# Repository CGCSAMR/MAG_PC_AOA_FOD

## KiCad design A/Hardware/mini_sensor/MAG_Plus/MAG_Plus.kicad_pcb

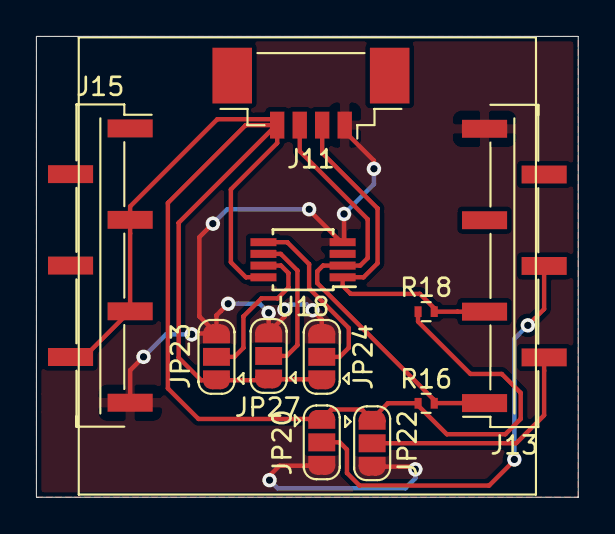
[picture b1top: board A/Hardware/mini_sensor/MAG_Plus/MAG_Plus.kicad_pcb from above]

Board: 2 copper layers, 30.1 x 25.6 mm, 11 parts (0 on the bottom side), 9 nets.

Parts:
J11: Conn_01x04_Male; Molex_PicoBlade_53398-0471_04x1.25mm_Straight
J13, J15: Conn_01x07_Female; Pin_Header_Straight_1x07_Pitch2.54mm_SMD_Pin1Right
JP20, JP22, JP23, JP24, JP27: Jumper_3_Open; SolderJumper-3_P1.3mm_Open_RoundedPad1.0x1.5mm
R16, R18: R; R_0402
U18: MCP9804_MSOP; MSOP-8_3x3mm_Pitch0.65mm

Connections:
GND: J11.1, J13.7, J15.7, JP20.3, JP22.3, JP23.3, JP24.3, JP27.3, U18.4
MAG2_A0: JP23.2, U18.7
MAG2_A1: JP27.2, U18.6
MAG2_A2: JP24.2, U18.5
MAG2_BIT0: J13.4, JP20.2
MAG2_BIT1: J13.2, JP22.2
MAG_3V3: J11.4, J15.3, J15.5, J15.6, JP20.1, JP22.1, JP23.1, JP24.1, JP27.1, R16.1, R18.1, U18.8
RPI_SCL: J11.3, J13.1, R16.2, U18.2
RPI_SDA: J11.2, J13.3, R18.2, U18.1

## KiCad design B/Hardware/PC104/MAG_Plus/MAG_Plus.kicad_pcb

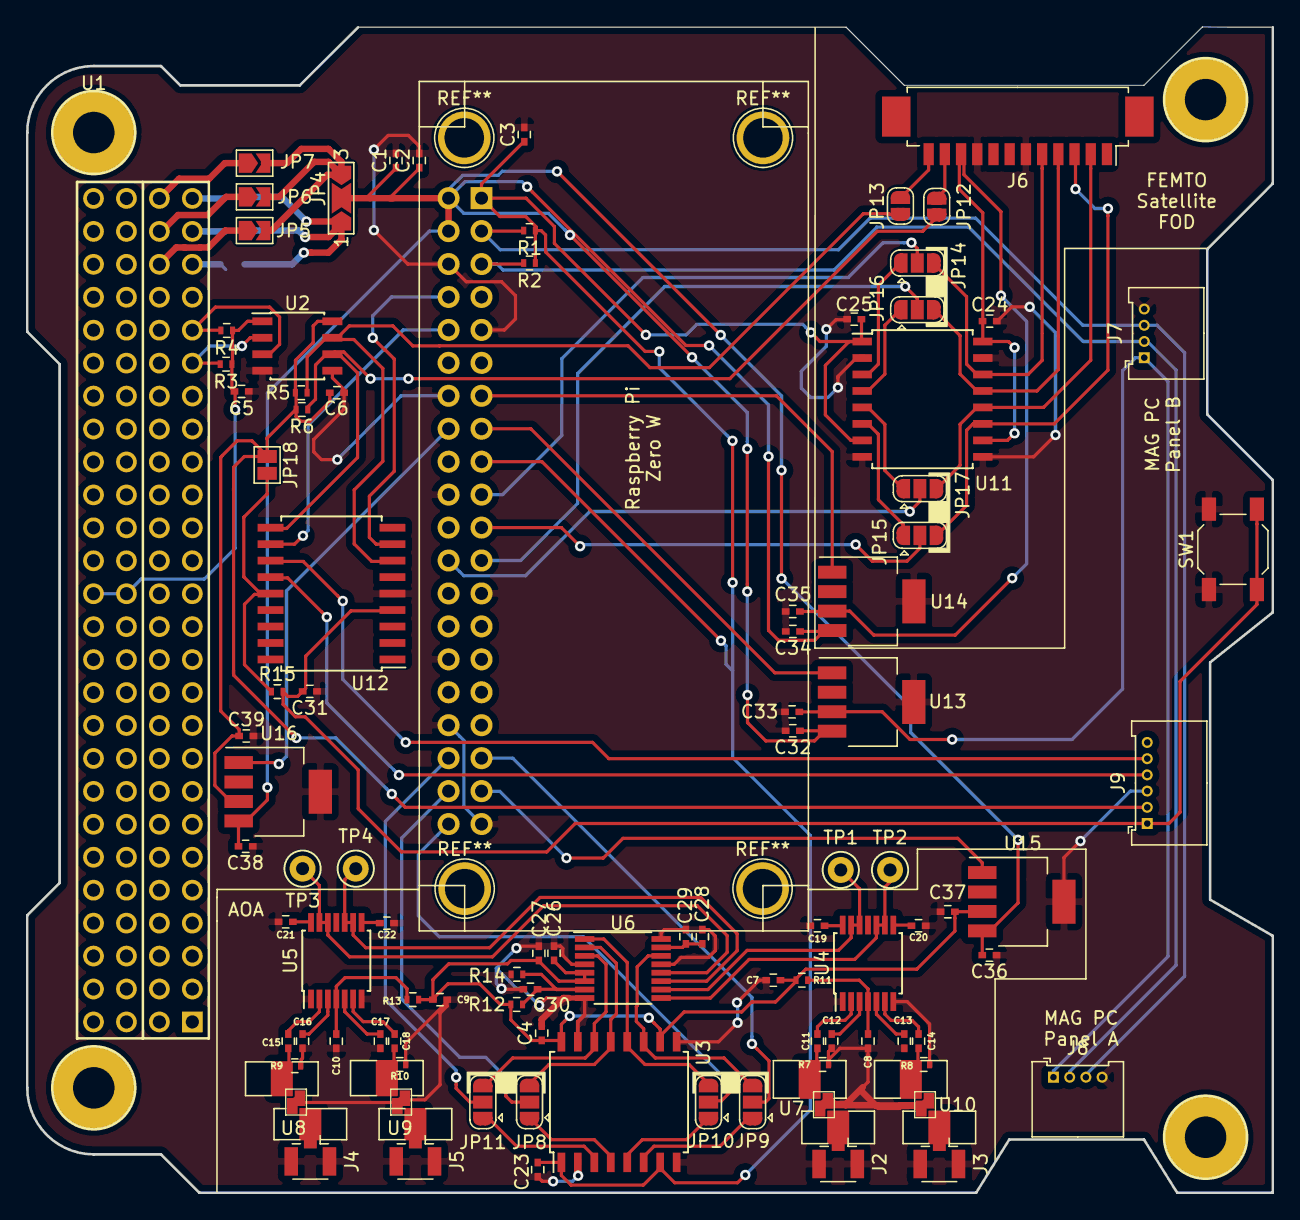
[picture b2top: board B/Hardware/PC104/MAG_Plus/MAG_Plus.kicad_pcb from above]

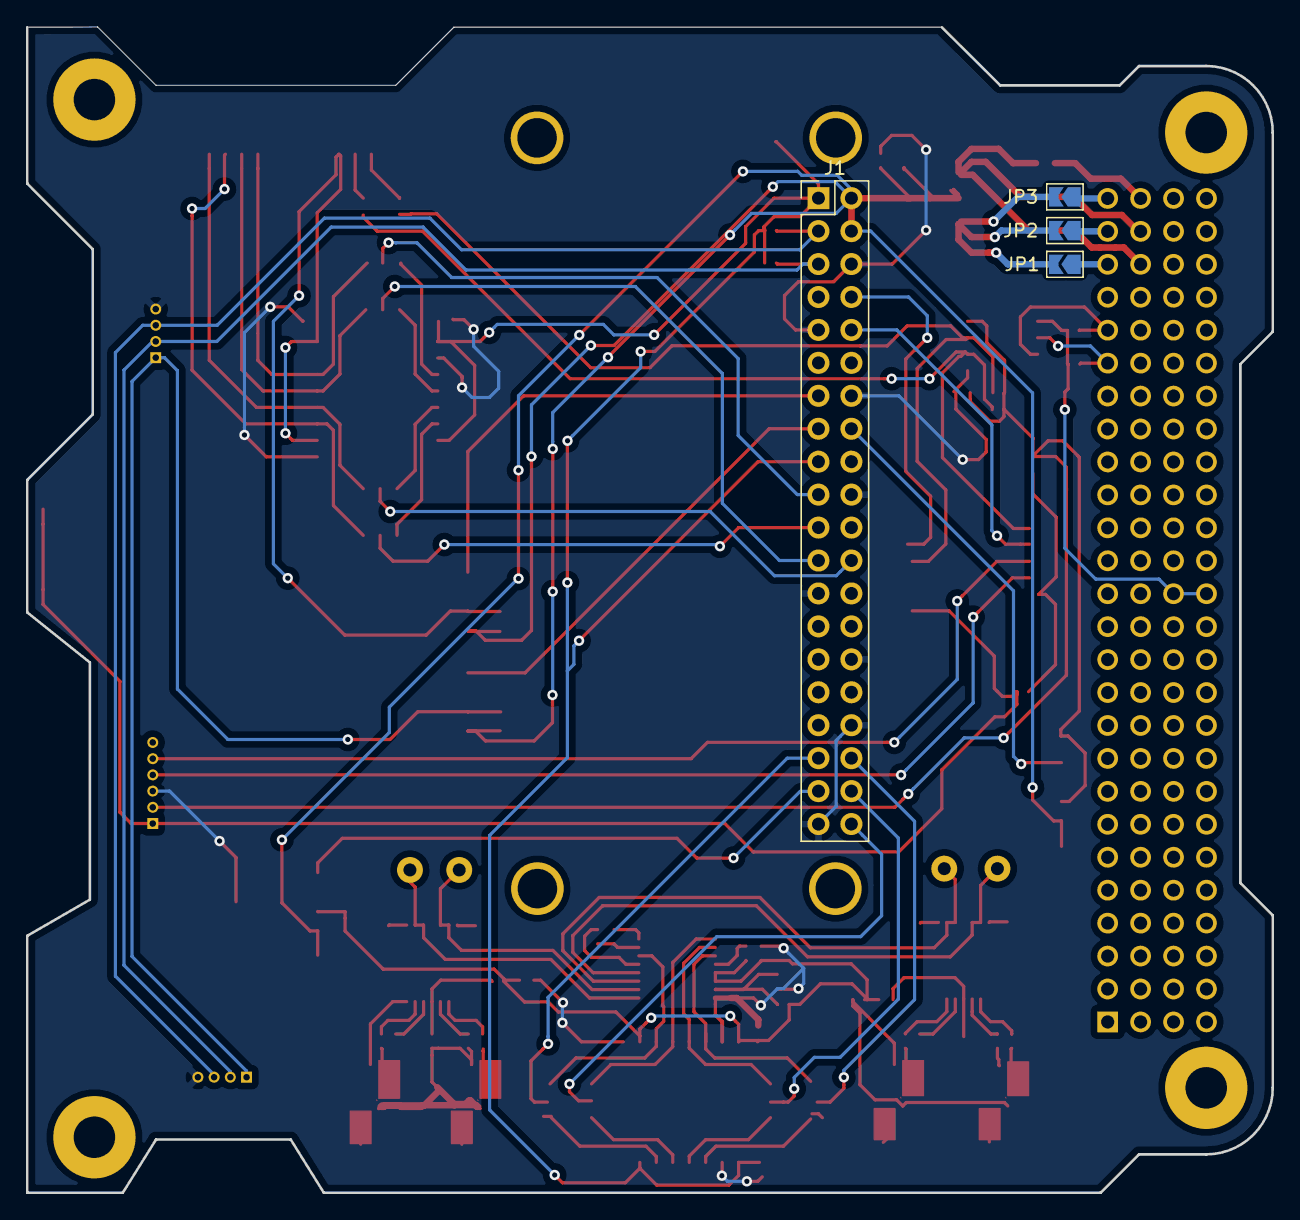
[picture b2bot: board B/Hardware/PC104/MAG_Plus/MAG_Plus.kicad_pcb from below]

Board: 2 copper layers, 96.0 x 89.9 mm, 102 parts (4 on the bottom side), 86 nets.

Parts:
C1, C2, C3, C4, C5, C6, C23, C24, C25, C26, C27, C28, C29, C30, C31, C32, C33, C34, C35, C36, C37, C38, C39: C; C_0402
C7, C8, C9, C10, C11, C12, C13, C14, C15, C16, C17, C18, C19, C20, C21, C22: C_Small; C_0402
J1: RPi_GPIO; Pin_Header_Straight_2x20_Pitch2.54mm
J2, J3, J4, J5: U.FL-R-SMT(01); U.FL_Hirose_U.FL-R-SMT-1_Vertical
J6: Conn_01x12_Male; Molex_PicoBlade_53261-1271_12x1.25mm_Angled
J7, J8: Conn_01x04_Male; Molex_PicoBlade_53048-0410_04x1.25mm_Angled
J9: Conn_01x06_Male; Molex_PicoBlade_53048-0610_06x1.25mm_Angled
JP1, JP2, JP3, JP5, JP6, JP7: Jumper_2_Open; SolderJumper-2_P1.3mm_Open_TrianglePad1.0x1.5mm
JP4: Jumper_3_Open; SolderJumper-3_P2.0mm_Open_TrianglePad1.0x1.5mm_NumberLabels
JP8, JP9, JP10, JP11, JP14, JP15, JP16, JP17: Jumper_3_Open; SolderJumper-3_P1.3mm_Open_RoundedPad1.0x1.5mm
JP12, JP13: Jumper_2_Open; SolderJumper-2_P1.3mm_Open_RoundedPad1.0x1.5mm
JP18: Jumper_2_Open; SolderJumper-2_P1.3mm_Open_Pad1.0x1.5mm
R1, R2, R3, R4, R5, R6, R12, R14, R15: R; R_0402
R7, R8, R9, R10, R11, R13: R_Small; R_0402
SW1: SW_Push; SW_SPST_SKQG
TP1, TP2, TP3, TP4: TestPoint; Test_Point_Keystone_5000-5004_Miniature
U1: Payload; PC104-Standard
U2: ISO1540; SOIC-8_3.9x4.9mm_Pitch1.27mm
U3, U11: ISO7341C; SOIC-16W_7.5x10.3mm_Pitch1.27mm
U4, U5: AD8302; TSSOP-14_4.4x5mm_Pitch0.65mm
U6: AD7904BRUZ-REEL7; TSSOP-16_4.4x5mm_Pitch0.65mm
U7, U8, U9, U10: QPQ1906SR
U12: PIC16F1847-I_SO; SOIC-18W_7.5x11.6mm_Pitch1.27mm
U13, U14, U16: LP38693MP-3.3; SOT-223-5
U15: LP38693MP-5.0; SOT-223-5

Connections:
3V3IN: JP1.2, JP2.2, JP3.2, JP4.1
5VIN: JP4.3, JP5.2, JP6.2, JP7.2
ANT1_IN: J2.1, U7.1
ANT1_OUT: C11.1, R7.1, U7.2
ANT2_IN: J3.1, U10.1
ANT2_OUT: C14.1, R8.2, U10.2
ANT3_IN: J4.1, U8.1
ANT3_OUT: C15.1, R9.1, U8.2
ANT4_IN: J5.1, U9.1
ANT4_OUT: C18.1, R10.2, U9.2
AOA_3V3: C28.1, C29.1, U6.15
AOA_5V: C4.1, C7.2, C9.2, C26.1, C27.1, C37.1, R11.1, R12.2, R13.1, U3.10, U3.16, U6.5, U6.6, U15.3
AOA_CLK: JP10.3, U3.12, U6.1
AOA_EN: J1.37, U15.1
AOA_MISO: JP9.3, U3.11, U6.14
AOA_MOSI: JP8.3, U3.13, U6.2
AOA_SS: JP11.3, U3.14, U6.3
CLK0: J1.23, JP16.2
CLK1: J1.40, JP10.2
CSP_SCL: R4.2, U1.43, U2.3
CSP_SDA: R3.2, U1.41, U2.2
FOD_3V3: C24.1, C35.1, J6.10, U11.10, U11.16, U14.3
FOD_CS: J6.2, JP17.3, U11.12
FOD_EN: J1.13, U14.1
FOD_MISO: J6.3, JP15.3, U11.11
FOD_MOSI: J6.5, JP14.3, U11.14
FOD_SCK: J6.4, JP16.3, U11.13
FOD_SCL: J6.11, JP12.2
FOD_SDA: J6.12, JP13.2
GND: C1.2, C2.2, C3.2, C4.2, C5.2, C6.2, C7.1, C8.1, C9.1, C10.1, C12.1, C13.1, C16.1, C17.1, C19.2, C20.2, C21.2, C22.2, C23.2, C24.2, C25.2, C26.2, C27.2, C28.2, C29.2, C30.1, C31.1, C32.2, C33.2, C34.2, C35.2, C36.2, C37.2, C38.2, C39.2, J1.6, J1.9, J1.14, J1.20, J1.25, J1.30, J1.34, J1.39, J2.2, J3.2, J4.2, J5.2, J6.6, J6.9, J7.4, J8.4, J9.3, R7.2, R8.1, R9.2, R10.1, R14.2, SW1.1, U2.4, U2.5, U3.2, U3.8, U3.9, U3.15, U4.1, U4.7, U5.1, U5.7, U6.4, U6.8, U6.13, U6.16, U7.3, U8.3, U9.3, U10.3, U11.2, U11.8, U11.9, U11.15, U12.5, U13.5, U14.5, U15.5, U16.5
ICSPCLK: J9.5, U12.12
ICSPDAT: J9.4, U12.13
MAG_3V3: C33.1, J7.1, J8.1, U13.3
MAG_EN: J1.15, U13.1
MCLR: C31.2, J9.1, R15.2, SW1.2, U12.4
MISO0: J1.21, JP15.2
MISO1: J1.35, JP9.2
MOSI0: J1.19, JP14.2
MOSI1: J1.38, JP8.2
unnamed: C8.2, R11.2, U4.4
unnamed: C10.2, R13.2, U5.4
unnamed: C11.2, U4.2
unnamed: C12.2, U4.3
unnamed: C13.2, U4.5
unnamed: C14.2, U4.6
unnamed: C15.2, U5.2
unnamed: C16.2, U5.3
unnamed: C17.2, U5.5
unnamed: C18.2, U5.6
unnamed: C19.1, U4.14
unnamed: C20.1, U4.8
unnamed: C21.1, U5.14
unnamed: C22.1, U5.8
unnamed: C30.2, R12.1, R14.1, U6.7
OUT1_3V3: JP1.1, U1.47
OUT2_3V3: JP2.1, U1.49
OUT3_3V3: JP3.1, U1.51
OUT4_5V0: JP5.1, U1.48
OUT5_5V0: JP6.1, U1.50
OUT6_5V0: JP7.1, U1.52
PIC_3V3: C6.1, C39.1, J9.2, JP18.1, R5.1, R6.1, U2.8, U16.3
PIC_3V3J: JP18.2, R15.1, U12.14
PIC_EN: J1.16, U16.1
PIC_SCL: JP12.1, R6.2, U2.6, U12.10
PIC_SDA: JP13.1, R5.2, U2.7, U12.7
RPI_3V3: C3.1, C23.1, C25.1, J1.1, J1.17, R1.1, R2.1, U3.1, U3.7, U11.1, U11.7
RPI_RX: J1.10, U12.11
RPI_SCL: J1.5, J7.2, J8.2, R2.2
RPI_SDA: J1.3, J7.3, J8.3, R1.2
RPI_TX: J1.8, U12.8
SAT_3V3: C5.1, R3.1, R4.1, U1.79, U1.80, U2.1
SS00: J1.24, JP17.2
SS10: J1.36, JP11.2
VIN: C1.1, C2.1, C32.1, C34.1, C36.1, C38.1, J1.2, J1.4, JP4.2, U13.4, U14.4, U15.4, U16.4
VMAG1: TP1.1, U4.12, U4.13, U6.10
VMAG2: TP3.1, U5.12, U5.13, U6.12
VPHS1: TP2.1, U4.9, U4.10, U6.9
VPHS2: TP4.1, U5.9, U5.10, U6.11
iaRPI_CLK: JP10.1, U3.5
iaRPI_MISO: JP9.1, U3.6
iaRPI_MOSI: JP8.1, U3.4
iaRPI_SS0: JP11.1, U3.3
ifRPI_CLK: JP16.1, U11.4
ifRPI_MISO: JP15.1, U11.6
ifRPI_MOSI: JP14.1, U11.3
ifRPI_SS0: JP17.1, U11.5
